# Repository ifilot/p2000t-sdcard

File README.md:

# P2000T SD-CARD cartridge

## Table of contents

* [Purpose](#purpose)
* [Downloads](#downloads)
* [How it functions](#how-it-functions)
* [Images](#images)
* [Commands](#commands)
* [Compilation instructions](#compilation-instructions)
* [Repository contents](#repository-contents)
* [Building the hardware](#building-the-hardware)
* [Ordering a cartridge](#ordering-a-cartridge)
* [Internal SD-card board](#internal-sd-card-board)
* [Formatting SD-card](#formatting-sd-card)
* [License](#license)

> [!TIP] 
> Have questions or comments about the **P2000T SD-card cartridge**? Join
> the conversation and chat with the developers on our [Discord
> server](https://discord.gg/YtzJTWYAxy).

## YouTube

Check out the YouTube video below for a detailed review of the SD-card cartridge.

## Purpose

Perhaps the most elegant solution for loading CAS files into your P2000T or
making backups of your tapes is via a cartridge that hosts an SD-card slot. Even
the smallest SD-cards have enough capacity to store the complete P2000T tape
archive. Reading from such an SD-card is non-trivial and requires both a
hardware solution to interface with the I/O port of the P2000T as well as a
software solution to navigate through the files hosted on a FAT32 partition.
This repository contains the PCB for interfacing a P2000T with an SD-card and
the necessary software routines to grab .CAS files from said SD card and load
them into memory.

> [!TIP]
> **Documentation**
> * Detailed documentation included how-to procedures can be found [here](https://www.philips-p2000t.nl/cartridges/sdcard-cartridge.html#sdcard-cartridge)
> * There is also a [manual in Dutch](https://github.com/ifilot/P2000T-SD-kaart-handleiding)  available.

## Downloads 

Read the section ["How it functions"](#how-it-functions) to understand what each
download file does.

> [!WARNING] 
> The files shown here cater specifically to PCB version 6 or later
> where the SD-card listens to I/O port 0x4X. Earlier version of the PCB are no
> longer actively maintained.

* [BASICBOOTSTRAP.BIN](https://github.com/ifilot/p2000t-sdcard/releases/download/latest-stable/BASICBOOTSTRAP.BIN)
* [FLASHER.BIN](https://github.com/ifilot/p2000t-sdcard/releases/download/latest-stable/FLASHER.BIN)
* [LAUNCHER.BIN](https://github.com/ifilot/p2000t-sdcard/releases/download/latest-stable/LAUNCHER.BIN)

> [!TIP]
> * Precompiled SD-card images, including flashing instructions, can be found [here](https://github.com/ifilot/p2000t-sdcard-image)
> * A list of PRG programs, specifically designed to operate with the SD-card cartridge, can be found [here](https://github.com/ifilot/p2000t-sdcard-cartridge-programs)

## How it functions

To interface with the SD-card, an SD-card slot is connected to the I/O port of
the P2000T. Interfacing with the SD-card proceeds via the SPI protocol which is
encoded in hardware (in contrast to bit-banging the protocol in software). From
the perspective of the P2000T, simple 1-byte instructions can be sent and
retrieved from the SD-card. By sending specific commands, data is sent or
retrieved from the SD-card.

While the SLOT2 cartridge (which hooks up to the I/O port of the P2000T) hosts
the circuitry to interface with the SD-card, a SLOT1 cartridge is required that
hosts the software. In order to run BASIC programs that are stored on the
SD-card as `.CAS` files, the regular BASIC environment **and** the required
routines to interface with the SD-card need to be present in memory. For this
reason, a modified version of the BASIC environment is used which upon boot will
load a launcher application from the ROM chip on the SLOT2 cartridge into main
memory. This launcher application allows the user to navigate the SD-card and
load BASIC programs into memory and run these. Detailed instructions on this
process are found [here](https://www.philips-p2000t.nl/cartridges/sdcard-cartridge.html#launching-cas-programs-from-the-sd-card-cartridge).

The launcher application needs to be placed on the ROM chip by means of a
flasher program. The flasher program is a different SLOT1 cartridge which can be
downloaded from the [download section](#downloads). The flasher program will
copy a `LAUNCHER.BIN` file from the root folder of the SD-card to the ROM chip
on the SLOT2 cartridge. This procedure is also used to update the launcher
application. Details on this process can be found [here](https://www.philips-p2000t.nl/cartridges/sdcard-cartridge.html#flashing-the-launcher-onto-the-rom-chip).

It is also possible to make copies of existing tapes to the SD-card. For this
purpose, a `CASDUMP.PRG` program is written. These special types of programs can
be loaded from the SD-card and executes via the launcher application. After
completion, one automatically returns to the launcher, allowing one to load one
of the freshly copied programs.

## Images

SLOT2 cartridge enclosure and populated PCB.

Screenshots of navigation and execution of .CAS files.

## Commands

Upon booting into the LAUNCHER application, the user interfaces with the SD-card
using a set of short commands. Below, the list of commands is provided

| **Command**         | **Description**                                                   |
| ------------------- | ------------------------------------------------------------------|
| `ls`                | List contents of current folder                                   |
| `lscas`             | List contents of current folder, listing contents of CAS files    |
| `cd <number>`       | Change directory                                                  |
| `run <number>`      | Run .CAS file                                                     |
| `hexdump <number>`  | Performs a 120-byte hexdump of a file                             |
| `fileinfo <number>` | Provides location details of a file                               |
| `ledtest`           | Performs a quick test on the read/write LEDs                      |
| `stack`             | Show current position of the stack pointer                        |
| `dump<XXXX>`        | Perform a 120-byte hexdump of main memory starting at `0xXXXX`    |
| `romdump<XXXX>`     | Perform a 120-byte hexdump of cartridge ROM starting at `0xXXXX`  |
| `ramdump<XXXX>`     | Perform a 120-byte hexdump of cartridge RAM starting at `0xXXXX`  |

Note that `<number>` needs to replaced with the specific number of a file. Users
who are familiar with command line interfaces are probably used to specifying
filenames rather than numbers. This reason this approach was chosen is mainly
because it is simpler to program and furthermore a bit quicker to type.

## Compilation instructions

Compilation is done using the [z88dk Docker](https://hub.docker.com/r/z88dk/z88dk)
by means of `compile.sh`. To compile the launcher, run

```bash
cd src
./compile launcher
```

and for the flasher utility

```bash
cd src
./compile flasher
```

## Repository contents

* [Cartridge cases](cases/)
* [PCB layout files (KiCAD)](pcb/port2-sdcard-interface/)
* [Modified BASIC ROM source files](basicmod/)
* [Launcher and Flasher programs](src/)
* [Custom programs](programs/)

## Building the hardware

### Gerber files

To create your own SLOT2 cartridge, download the GERBER files from
[here](pcb/port2-sdcard-interface/GERBERS/), put them in a `.ZIP` file and send
them to your favorite PCB print farm. The author of this repository mainly uses
[JLCPCB](https://jlcpcb.com/), but plenty of alternatives are available. The
SLOT2 PCB has four layers. It is recommended to apply an ENIG (gold) coating and
chamfer the edge connector for facile insertion into the P2000T. After ordering,
one needs to either hand-solder the components (which can be tricky for the SMD
chips) or alternatively make use of an assembly service by which the PCB print
farm will solder these components for you.

### PCB assembly service

The folder [pcb/port2-sdcard-interface](pcb/port2-sdcard-interface) contains
`port2-sdcard-interface_bom_bot.csv` and `port2-sdcard-interface-bottom-pos.csv`
which can be used for the JLCPCB assembly service. An example of the part
placement can be found in the image below. At the time of writing, two
components were unavailable, being the memory chip `62128` and a 0 ohm resistor,
which is the reason that these two parts are missing. Note that all through-hole
parts, e.g. LEDs, oscillator and PLCC32 socket, have to be hand-soldered in.

### Ordering a cartridge

It is also possible to order a cartridge (typically there are always a few
of them in stock). If you are interested, feel free to contact the author of
this repository at `ivo at ivofilot dot nl` to discuss pricing and shipping.

## Internal SD-card board

This project also includes an [internal SD-card
board](pcb/internal-sdcard-interface/) designed to mount on top of the main
baseboard inside the P2000T. In addition to the SD-card reader functionality,
the board also provides 64 KiB of additional memory, making it an all-in-one
solution.

To install this board, you will need two custom brackets. You can find the
necessary bracket files [here](brackets).

## Formatting SD-card

The way that the SD-card is formatted is critical. The SD-card needs be
formatted using a MBR/FAT32 partition. Often, directly formatting the SD-card
via Windows Explorer or similar works well, but sometimes a more rigorous
procedure is needed, which is explained below.

1. Type `WINDOWS + R` and run `CMD`.
2. Run `diskpart`.
3. Type `list disk` followed by `select disk <NR>` where `<NR>` corresponds to
   your SD-card.
4. Type `clean`. You get a response with `DiskPart succeeded in cleaning the
   disk.`.
5. Type `list volume`, followed by `select volume <ID>` where `<ID>` corresponds
   to your SD-card drive.
6. Type `convert mbr`. You should get the response `DiskPart successfully
   converted the selected disk to MBR format.`.
7. Type `create partition primary`. The response should be `DiskPart succeeded
   in creating the specified partition.`.
8. Finally, type `format fs=fat32 quick label="P2000T"`, after which the
   response is `DiskPart successfully formatted the volume.`.

Your SD-card should now be ready to work in the SD-cartridge. Of course, you
still need to copy files to it in order to load something of it.

## License

* All software is shared under the [GPL v3 license](https://www.gnu.org/licenses/gpl-3.0).
* All hardware (e.g. KiCAD files and .stl files) are shared under the [CERN-OHL-S license](https://ohwr.org/project/cernohl/-/wikis/uploads/819d71bea3458f71fba6cf4fb0f2de6b/cern_ohl_s_v2.txt).
* All documentation is shared under the [CC-BY-SA 4.0 license](https://creativecommons.org/licenses/by-sa/4.0/).

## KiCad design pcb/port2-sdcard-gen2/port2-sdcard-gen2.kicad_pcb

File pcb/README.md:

# PCB

This folder contains the PCBs for the [SLOT2 SD-card cartridge](port2-sdcard-interface) 
and also for a [SD-card interface prototype PCB](sdcard-prototype). 
The latter is only used for development purposes and can be ignored if one is 
solely interested in building a SLOT2 cartridge.

## Bill of materials

* 1 x CY62128ELL-45SXI
* 3 x 74HC00
* 2 x 74HC74
* 1 x 74HC163
* 2 x 74HC138
* 1 x 74HC123
* 2 x 74HC273
* 2 x 74HC32
* 1 x HC165
* 1 x HC595
* 1 x SST39SF010
* 1 x 74HC02
* 1 x 74HC85
* 1 x 16MHz crystal oscillator

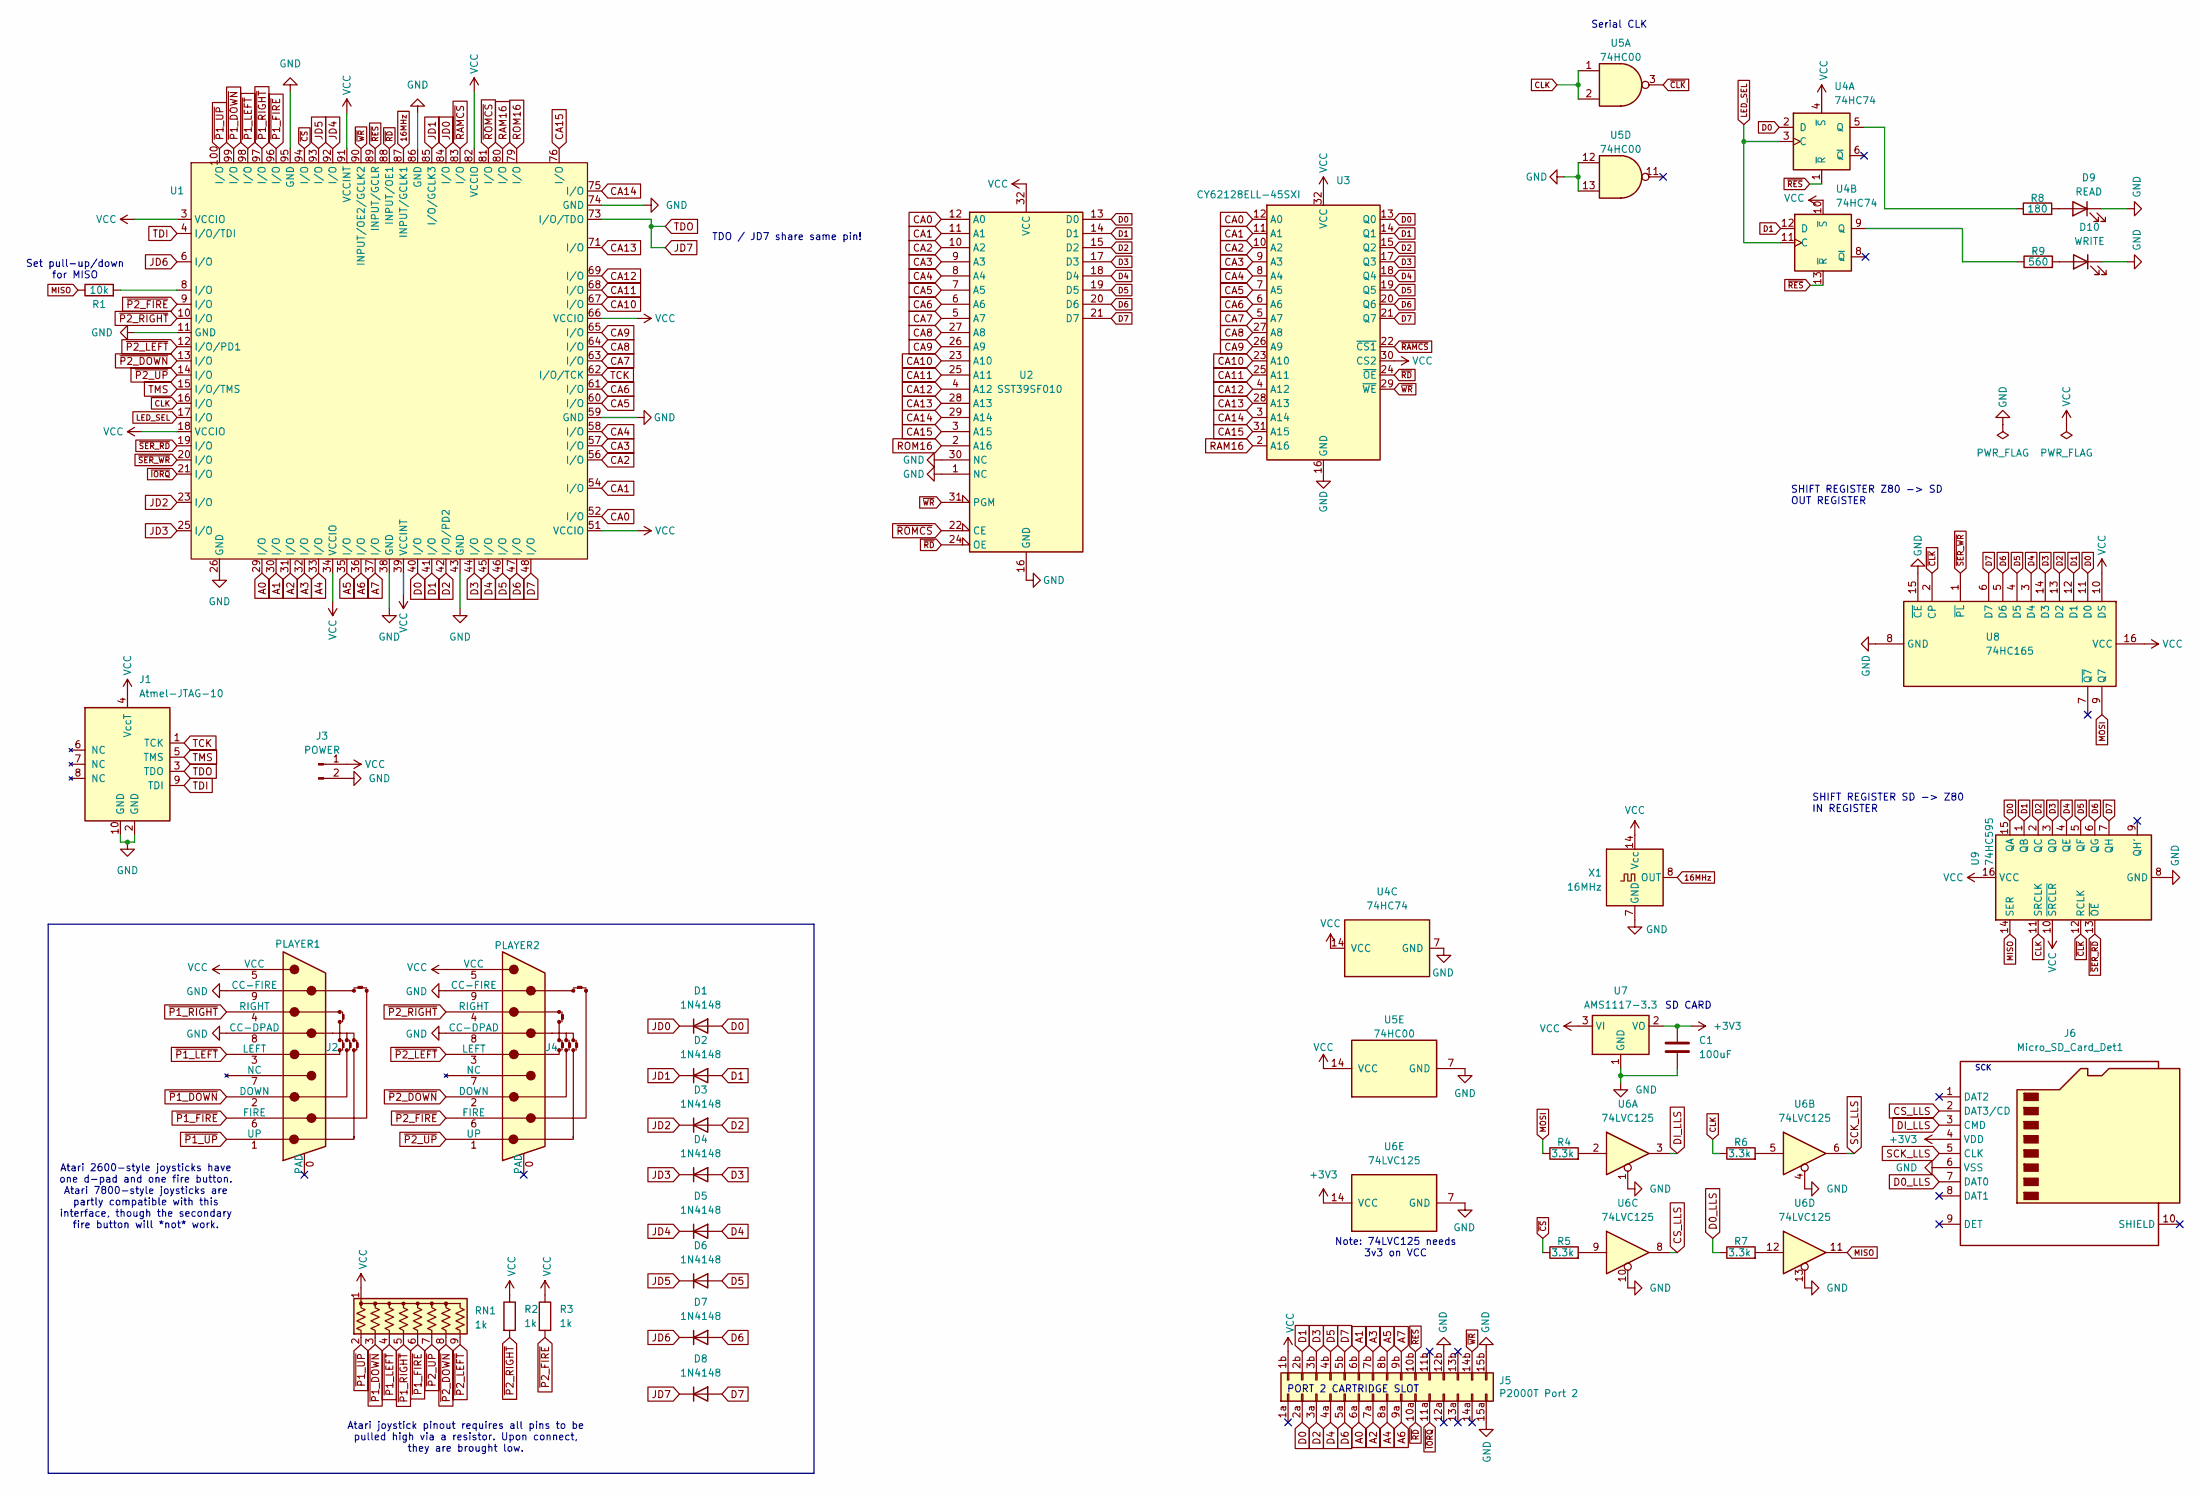
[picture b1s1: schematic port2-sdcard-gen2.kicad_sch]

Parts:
C1: 100uF; C_1206_3216Metric_Pad1.33x1.80mm_HandSolder; LCSC Part # C309030
D1, D2, D3, D4, D5, D6, D7, D8: 1N4148; D_DO-35_SOD27_P7.62mm_Horizontal
D9: READ; LED_0805_2012Metric_Pad1.15x1.40mm_HandSolder
D10: WRITE; LED_0805_2012Metric_Pad1.15x1.40mm_HandSolder
J1: Atmel-JTAG-10; IDC-Header_2x05_P2.54mm_Vertical
J2: PLAYER1; DSUB-9_Pins_Horizontal_P2.77x2.84mm_EdgePinOffset4.94mm_Hou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
J3: POWER
J4: PLAYER2; DSUB-9_Pins_Horizontal_P2.77x2.84mm_EdgePinOffset4.94mm_Hou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
J5: P2000T Port 2; p2000t_cartridge_edge
J6: Micro_SD_Card_Det1; CONN9_MSD-1_CUD; LCSC Part # C381082
R1: 10k; R_0805_2012Metric_Pad1.20x1.40mm_HandSolder
R2, R3: 1k; R_Axial_DIN0207_L6.3mm_D2.5mm_P7.62mm_Horizontal
R4, R5, R6, R7: 3.3k; R_0805_2012Metric_Pad1.20x1.40mm_HandSolder; LCSC Part # C407459
R8: 180; R_0805_2012Metric_Pad1.20x1.40mm_HandSolder; LCSC Part # C429158
R9: 560; R_0805_2012Metric_Pad1.20x1.40mm_HandSolder; LCSC Part # C429158
RN1: 1k; R_Array_SIP9
U1: TQFP-100_14x14mm_P0.5mm
U2: SST39SF010; PLCC-32_THT-Socket
U3: CY62128ELL-45SXI; SOP-32_11.305x20.495mm_P1.27mm; LCSC Part # C2840304
U4: 74HC74; SO-14_3.9x8.65mm_P1.27mm; LCSC Part # C27597
U5: 74HC00; SO-14_3.9x8.65mm_P1.27mm; LCSC Part # C699445
U6: 74LVC125; TSSOP-14_4.4x5mm_P0.65mm; LCSC Part # C7494906
U7: AMS1117-3.3; SOT-223-3_TabPin2; LCSC Part # C5346136
U8: 74HC165; SOIC-16_3.9x9.9mm_P1.27mm; LCSC Part # C5613
U9: 74HC595; SOIC-16_3.9x9.9mm_P1.27mm; LCSC Part # C5947
X1: 16MHz; Oscillator_DIP-14

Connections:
16MHz: U1.87 (INPUT/GCLK1), X1.8 (OUT)
+3V3: C1.1, J6.4 (VDD), U6.14 (VCC), U7.2 (VO)
A0: J5.6a, U1.29 (I/O)
A1: J5.6b, U1.30 (I/O)
A2: J5.7a, U1.31 (I/O)
A3: J5.7b, U1.32 (I/O)
A4: J5.8a, U1.33 (I/O)
A5: J5.8b, U1.35 (I/O)
A6: J5.9a, U1.36 (I/O)
A7: J5.9b, U1.37 (I/O)
CA0: U1.52 (I/O), U2.12 (A0), U3.12 (A0)
CA1: U1.54 (I/O), U2.11 (A1), U3.11 (A1)
CA2: U1.56 (I/O), U2.10 (A2), U3.10 (A2)
CA3: U1.57 (I/O), U2.9 (A3), U3.9 (A3)
CA4: U1.58 (I/O), U2.8 (A4), U3.8 (A4)
CA5: U1.60 (I/O), U2.7 (A5), U3.7 (A5)
CA6: U1.61 (I/O), U2.6 (A6), U3.6 (A6)
CA7: U1.63 (I/O), U2.5 (A7), U3.5 (A7)
CA8: U1.64 (I/O), U2.27 (A8), U3.27 (A8)
CA9: U1.65 (I/O), U2.26 (A9), U3.26 (A9)
CA10: U1.67 (I/O), U2.23 (A10), U3.23 (A10)
CA11: U1.68 (I/O), U2.25 (A11), U3.25 (A11)
CA12: U1.69 (I/O), U2.4 (A12), U3.4 (A12)
CA13: U1.71 (I/O), U2.28 (A13), U3.28 (A13)
CA14: U1.75 (I/O), U2.29 (A14), U3.3 (A14)
CA15: U1.76 (I/O), U2.3 (A15), U3.31 (A15)
CLK: R6.1, U1.16 (I/O), U5.1, U5.2, U9.11 (SRCLK)
CS_LLS: J6.2 (DAT3/CD), U6.8
D0: D1.2 (A), J5.2a, U1.40 (I/O), U2.13 (D0), U3.13 (Q0), U4.2 (D), U8.11 (D0), U9.15 (QA)
D0_LLS: J6.7 (DAT0), R7.1
D1: D2.2 (A), J5.2b, U1.41 (I/O), U2.14 (D1), U3.14 (Q1), U4.12 (D), U8.12 (D1), U9.1 (QB)
D2: D3.2 (A), J5.3a, U1.42 (I/O/PD2), U2.15 (D2), U3.15 (Q2), U8.13 (D2), U9.2 (QC)
D3: D4.2 (A), J5.3b, U1.44 (I/O), U2.17 (D3), U3.17 (Q3), U8.14 (D3), U9.3 (QD)
D4: D5.2 (A), J5.4a, U1.45 (I/O), U2.18 (D4), U3.18 (Q4), U8.3 (D4), U9.4 (QE)
D5: D6.2 (A), J5.4b, U1.46 (I/O), U2.19 (D5), U3.19 (Q5), U8.4 (D5), U9.5 (QF)
D6: D7.2 (A), J5.5a, U1.47 (I/O), U2.20 (D6), U3.20 (Q6), U8.5 (D6), U9.6 (QG)
D7: D8.2 (A), J5.5b, U1.48 (I/O), U2.21 (D7), U3.21 (Q7), U8.6 (D7), U9.7 (QH)
DI_LLS: J6.3 (CMD), U6.3
GND: C1.2, D9.1 (K), D10.1 (K), J1.2 (GND), J1.10 (GND), J2.8 (CC-DPAD), J2.9 (CC-FIRE), J3.2, J4.8 (CC-DPAD), J4.9 (CC-FIRE), J5.12b, J5.15a, J5.15b, J6.6 (VSS), U1.11 (GND), U1.26 (GND), U1.38 (GND), U1.43 (GND), U1.59 (GND), U1.74 (GND), U1.86 (GND), U1.95 (GND), U2.1 (NC), U2.16 (GND), U2.30 (NC), U3.16 (GND), U4.7 (GND), U5.7 (GND), U5.12, U5.13, U6.1, U6.4, U6.7 (GND), U6.10, U6.13, U7.1 (GND), U8.8 (GND), U8.15 (~CE), U9.8 (GND), X1.7 (GND)
JD0: D1.1 (K), U1.84 (I/O)
JD1: D2.1 (K), U1.85 (I/O/GCLK3)
JD2: D3.1 (K), U1.23 (I/O)
JD3: D4.1 (K), U1.25 (I/O)
JD4: D5.1 (K), U1.92 (I/O)
JD5: D6.1 (K), U1.93 (I/O)
JD6: D7.1 (K), U1.6 (I/O)
JD7: D8.1 (K), J1.3 (TDO), U1.73 (I/O/TDO)
LED_SEL: U1.17 (I/O), U4.3 (C), U4.11 (C)
MISO: R1.1, U6.11, U9.14 (SER)
MOSI: R4.1, U8.9 (Q7)
unnamed: D9.2 (A), R8.2
unnamed: D10.2 (A), R9.2
unnamed: R1.2, U1.8 (I/O)
unnamed: R4.2, U6.2
unnamed: R5.2, U6.9
unnamed: R6.2, U6.5
unnamed: R7.2, U6.12
unnamed: R8.1, U4.5 (Q)
unnamed: R9.1, U4.9 (Q)
RAM16: U1.80 (I/O), U3.2 (A16)
ROM16: U1.79 (I/O), U2.2 (A16)
SCK_LLS: J6.5 (CLK), U6.6
TCK: J1.1 (TCK), U1.62 (I/O/TCK)
TDI: J1.9 (TDI), U1.4 (I/O/TDI)
TMS: J1.5 (TMS), U1.15 (I/O/TMS)
VCC: J1.4 (VccT), J2.5 (VCC), J3.1, J4.5 (VCC), J5.1b, R2.1, R3.1, RN1.1 (common), U1.3 (VCCIO), U1.18 (VCCIO), U1.34 (VCCIO), U1.39 (VCCINT), U1.51 (VCCIO), U1.66 (VCCIO), U1.82 (VCCIO), U1.91 (VCCINT), U2.32 (VCC), U3.30 (CS2), U3.32 (VCC), U4.4 (~S), U4.10 (~S), U4.14 (VCC), U5.14 (VCC), U7.3 (VI), U8.10 (DS), U8.16 (VCC), U9.10 (~SRCLR), U9.16 (VCC), X1.14 (Vcc)
~CLK: U5.3, U8.2 (CP), U9.12 (RCLK)
~CS: R5.1, U1.94 (I/O)
~IORQ: J5.11a, U1.21 (I/O)
~P1_DOWN: J2.2 (DOWN), RN1.3 (R2), U1.99 (I/O)
~P1_FIRE: J2.6 (FIRE), RN1.6 (R5), U1.96 (I/O)
~P1_LEFT: J2.3 (LEFT), RN1.4 (R3), U1.98 (I/O)
~P1_RIGHT: J2.4 (RIGHT), RN1.5 (R4), U1.97 (I/O)
~P1_UP: J2.1 (UP), RN1.2 (R1), U1.100 (I/O)
~P2_DOWN: J4.2 (DOWN), RN1.8 (R7), U1.13 (I/O)
~P2_FIRE: J4.6 (FIRE), R3.2, U1.9 (I/O)
~P2_LEFT: J4.3 (LEFT), RN1.9 (R8), U1.12 (I/O/PD1)
~P2_RIGHT: J4.4 (RIGHT), R2.2, U1.10 (I/O)
~P2_UP: J4.1 (UP), RN1.7 (R6), U1.14 (I/O)
~RAMCS: U1.83 (I/O), U3.22 (~CS1)
~RD: J5.10a, U1.88 (INPUT/OE1), U2.24 (OE), U3.24 (~OE)
~RES: J5.10b, U1.89 (INPUT/GCLR), U4.1 (~R), U4.13 (~R)
~ROMCS: U1.81 (I/O), U2.22 (CE)
~SER_RD: U1.19 (I/O), U9.13 (~OE)
~SER_WR: U1.20 (I/O), U8.1 (~PL)
~WR: J5.14b, U1.90 (INPUT/OE2/GCLK2), U2.31 (PGM), U3.29 (~WE)

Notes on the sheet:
SHIFT REGISTER Z80 -> SD OUT REGISTER
Serial CLK
PORT 2 CARTRIDGE SLOT
SCK
SHIFT REGISTER SD -> Z80 IN REGISTER
Atari 2600-style joysticks have one d-pad and one fire button. Atari 7800-style joysticks are partly compatible with this interface, though the secondary fire button will *not* work.
SD CARD
TDO / JD7 share same pin!
Atari joystick pinout requires all pins to be pulled high via a resistor. Upon connect, they are brought low.
Set pull-up/down for MISO
Note: 74LVC125 needs 3v3 on VCC

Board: 2 copper layers, 36 parts (31 on the bottom side), 86 nets, no tracks yet.

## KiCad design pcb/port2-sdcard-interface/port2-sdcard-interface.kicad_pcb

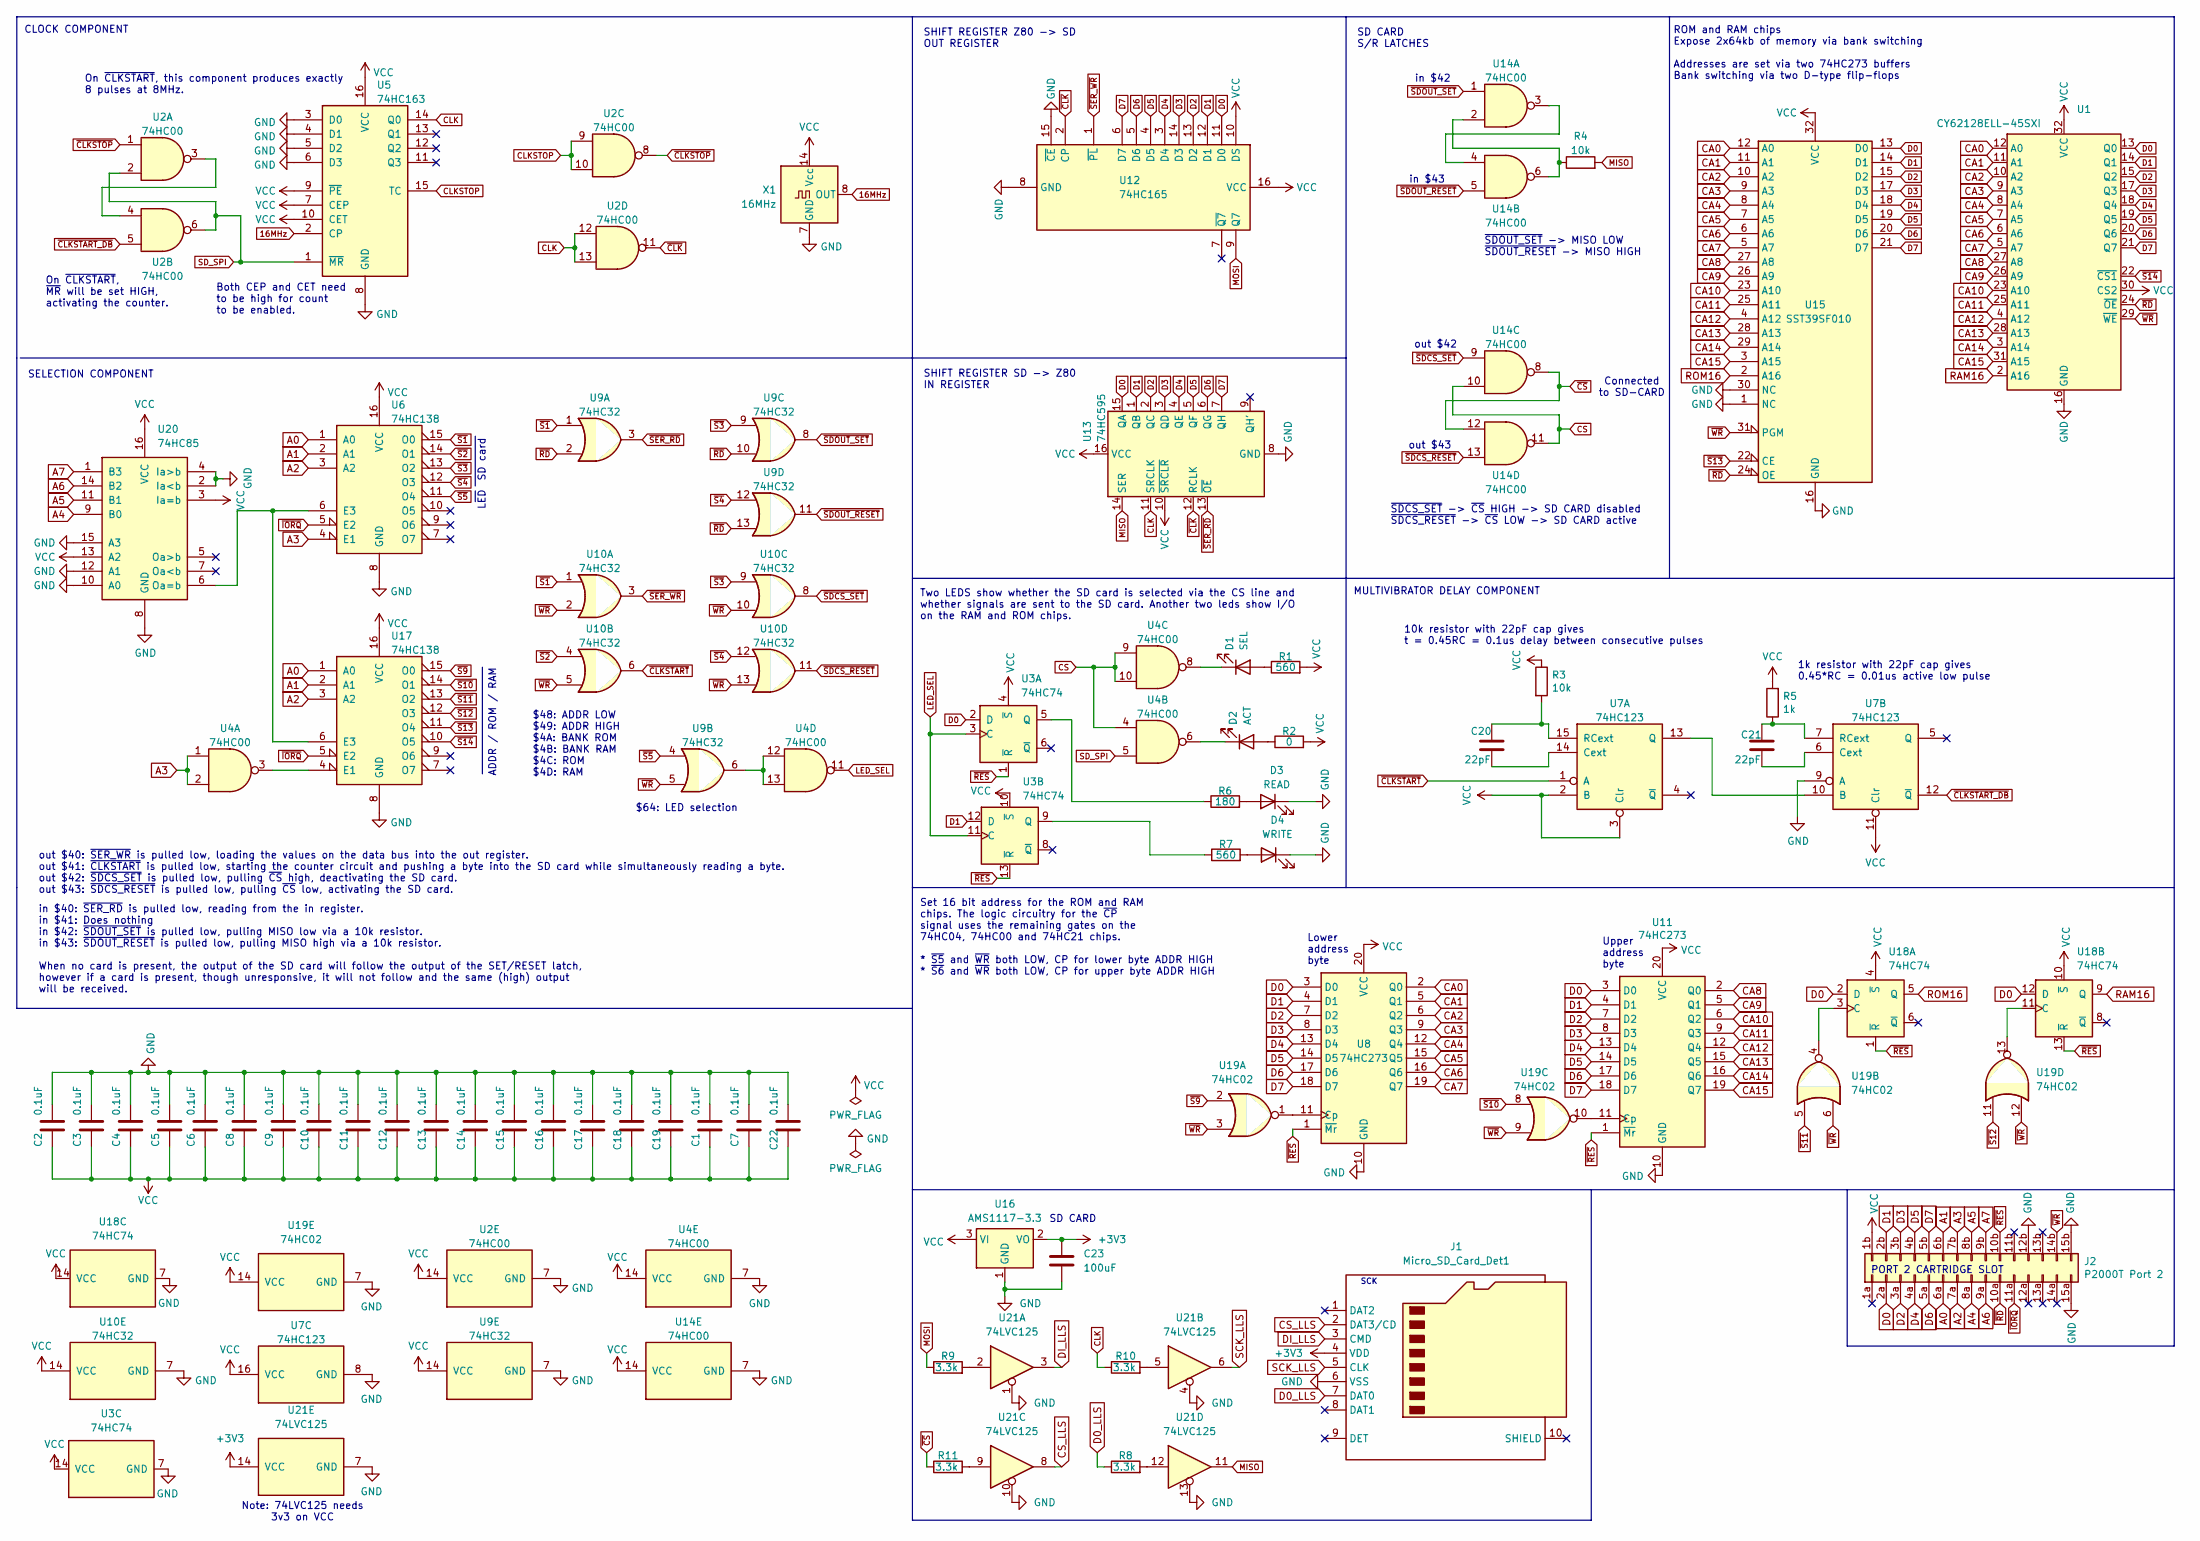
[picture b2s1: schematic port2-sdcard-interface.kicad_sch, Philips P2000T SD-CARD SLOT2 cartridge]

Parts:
C1, C2, C3, C4, C5, C6, C7, C8, C9, C10, C11, C12, C13, C14, C15, C16, C17, C18, C19, C22: 0.1uF; C_0805_2012Metric_Pad1.18x1.45mm_HandSolder; LCSC Part # C126469
C20, C21: 22pF; C_0805_2012Metric_Pad1.18x1.45mm_HandSolder; LCSC Part # C525286
C23: 100uF; C_1206_3216Metric_Pad1.33x1.80mm_HandSolder; LCSC Part # C309030
D1: SEL; LED_D5.0mm
D2: ACT; LED_D5.0mm
D3: READ; LED_D5.0mm
D4: WRITE; LED_D5.0mm
J1: Micro_SD_Card_Det1; CONN9_MSD-1_CUD; LCSC Part # C381082
J2: P2000T Port 2; p2000t_cartridge_edge
R1, R7: 560; R_0805_2012Metric_Pad1.20x1.40mm_HandSolder; LCSC Part # C429158
R2: 0; R_0805_2012Metric_Pad1.20x1.40mm_HandSolder; LCSC Part # C431818
R3, R4: 10k; R_0805_2012Metric_Pad1.20x1.40mm_HandSolder; LCSC Part # C5159708
R5: 1k; R_0805_2012Metric_Pad1.20x1.40mm_HandSolder; LCSC Part # C5123594
R6: 180; R_0805_2012Metric_Pad1.20x1.40mm_HandSolder; LCSC Part # C429158
R8, R9, R10, R11: 3.3k; R_0805_2012Metric_Pad1.20x1.40mm_HandSolder; LCSC Part # C407459
U1: CY62128ELL-45SXI; SSOP-32_11.305x20.495mm_P1.27mm; LCSC Part # C2840304
U2, U4, U14: 74HC00; SO-14_3.9x8.65mm_P1.27mm; LCSC Part # C699445
U3, U18: 74HC74; SO-14_3.9x8.65mm_P1.27mm; LCSC Part # C27597
U5: 74HC163; SOIC-16_3.9x9.9mm_P1.27mm; LCSC Part # C338758
U6, U17: 74HC138; SOIC-16_3.9x9.9mm_P1.27mm; LCSC Part # C5602
U7: 74HC123; SOIC-16_3.9x9.9mm_P1.27mm; LCSC Part # C5597
U8, U11: 74HC273; SOIC-20W_7.5x12.8mm_P1.27mm; LCSC Part # C131486
U9, U10: 74HC32; SO-14_3.9x8.65mm_P1.27mm; LCSC Part # C5632
U12: 74HC165; SOIC-16_3.9x9.9mm_P1.27mm; LCSC Part # C5613
U13: 74HC595; SOIC-16_3.9x9.9mm_P1.27mm; LCSC Part # C5947
U15: SST39SF010; PLCC-32_THT-Socket
U16: AMS1117-3.3; SOT-223-3_TabPin2; LCSC Part # C5346136
U19: 74HC02; SO-14_3.9x8.65mm_P1.27mm; LCSC Part # C5588
U20: 74HC85; SOIC-16_3.9x9.9mm_P1.27mm; LCSC Part # C5953
U21: 74LVC125; TSSOP-14_4.4x5mm_P0.65mm; LCSC Part # C7494906
X1: 16MHz; Oscillator_DIP-14

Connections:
16MHz: U5.2 (CP), X1.8 (OUT)
+3V3: C23.1, J1.4 (VDD), U16.2 (VO), U21.14 (VCC)
A0: J2.6a, U6.1 (A0), U17.1 (A0)
A1: J2.6b, U6.2 (A1), U17.2 (A1)
A2: J2.7a, U6.3 (A2), U17.3 (A2)
A3: J2.7b, U4.1, U4.2, U6.4 (E1)
A4: J2.8a, U20.9 (B0)
A5: J2.8b, U20.11 (B1)
A6: J2.9a, U20.14 (B2)
A7: J2.9b, U20.1 (B3)
CA0: U1.12 (A0), U8.2 (Q0), U15.12 (A0)
CA1: U1.11 (A1), U8.5 (Q1), U15.11 (A1)
CA2: U1.10 (A2), U8.6 (Q2), U15.10 (A2)
CA3: U1.9 (A3), U8.9 (Q3), U15.9 (A3)
CA4: U1.8 (A4), U8.12 (Q4), U15.8 (A4)
CA5: U1.7 (A5), U8.15 (Q5), U15.7 (A5)
CA6: U1.6 (A6), U8.16 (Q6), U15.6 (A6)
CA7: U1.5 (A7), U8.19 (Q7), U15.5 (A7)
CA8: U1.27 (A8), U11.2 (Q0), U15.27 (A8)
CA9: U1.26 (A9), U11.5 (Q1), U15.26 (A9)
CA10: U1.23 (A10), U11.6 (Q2), U15.23 (A10)
CA11: U1.25 (A11), U11.9 (Q3), U15.25 (A11)
CA12: U1.4 (A12), U11.12 (Q4), U15.4 (A12)
CA13: U1.28 (A13), U11.15 (Q5), U15.28 (A13)
CA14: U1.3 (A14), U11.16 (Q6), U15.29 (A14)
CA15: U1.31 (A15), U11.19 (Q7), U15.3 (A15)
CLK: R10.1, U2.12, U2.13, U5.14 (Q0), U13.11 (SRCLK)
CLKSTOP: U2.9, U2.10, U5.15 (TC)
CS: U4.4, U4.9, U4.10, U14.10, U14.11
CS_LLS: J1.2 (DAT3/CD), U21.8
D0: J2.2a, U1.13 (Q0), U3.2 (D), U8.3 (D0), U11.3 (D0), U12.11 (D0), U13.15 (QA), U15.13 (D0), U18.2 (D), U18.12 (D)
D0_LLS: J1.7 (DAT0), R8.1
D1: J2.2b, U1.14 (Q1), U3.12 (D), U8.4 (D1), U11.4 (D1), U12.12 (D1), U13.1 (QB), U15.14 (D1)
D2: J2.3a, U1.15 (Q2), U8.7 (D2), U11.7 (D2), U12.13 (D2), U13.2 (QC), U15.15 (D2)
D3: J2.3b, U1.17 (Q3), U8.8 (D3), U11.8 (D3), U12.14 (D3), U13.3 (QD), U15.17 (D3)
D4: J2.4a, U1.18 (Q4), U8.13 (D4), U11.13 (D4), U12.3 (D4), U13.4 (QE), U15.18 (D4)
D5: J2.4b, U1.19 (Q5), U8.14 (D5), U11.14 (D5), U12.4 (D5), U13.5 (QF), U15.19 (D5)
D6: J2.5a, U1.20 (Q6), U8.17 (D6), U11.17 (D6), U12.5 (D6), U13.6 (QG), U15.20 (D6)
D7: J2.5b, U1.21 (Q7), U8.18 (D7), U11.18 (D7), U12.6 (D7), U13.7 (QH), U15.21 (D7)
DI_LLS: J1.3 (CMD), U21.3
GND: C1.2, C2.2, C3.2, C4.2, C5.2, C6.2, C7.2, C8.2, C9.2, C10.2, C11.2, C12.2, C13.2, C14.2, C15.2, C16.2, C17.2, C18.2, C19.2, C22.2, C23.2, D3.1 (K), D4.1 (K), J1.6 (VSS), J2.12b, J2.15a, J2.15b, U1.16 (GND), U2.7 (GND), U3.7 (GND), U4.7 (GND), U5.3 (D0), U5.4 (D1), U5.5 (D2), U5.6 (D3), U5.8 (GND), U6.8 (GND), U7.8 (GND), U7.9 (A), U8.10 (GND), U9.7 (GND), U10.7 (GND), U11.10 (GND), U12.8 (GND), U12.15 (~CE), U13.8 (GND), U14.7 (GND), U15.1 (NC), U15.16 (GND), U15.30 (NC), U16.1 (GND), U17.8 (GND), U18.7 (GND), U19.7 (GND), U20.2 (Ia<b), U20.4 (Ia>b), U20.8 (GND), U20.10 (A0), U20.12 (A1), U20.15 (A3), U21.1, U21.4, U21.7 (GND), U21.10, U21.13, X1.7 (GND)
LED_SEL: U3.3 (C), U3.11 (C), U4.11
MISO: R4.2, U13.14 (SER), U21.11
MOSI: R9.1, U12.9 (Q7)
unnamed: D1.2 (A), R1.1
unnamed: D1.1 (K), U4.8
unnamed: D2.2 (A), R2.1
unnamed: D2.1 (K), U4.6
unnamed: D3.2 (A), R6.2
unnamed: D4.2 (A), R7.2
unnamed: R4.1, U14.2, U14.6
unnamed: R8.2, U21.12
unnamed: R9.2, U21.2
unnamed: R10.2, U21.5
unnamed: R11.2, U21.9
unnamed: U2.3, U2.4
unnamed: R6.1, U3.5 (Q)
unnamed: R7.1, U3.9 (Q)
unnamed: U4.12, U4.13, U9.6
unnamed: C20.1, U7.14 (Cext)
unnamed: U7.10 (B), U7.13 (Q)
unnamed: C20.2, R3.2, U7.15 (RCext)
unnamed: C21.1, U7.6 (Cext)
unnamed: C21.2, R5.1, U7.7 (RCext)
unnamed: U8.11 (Cp), U19.1
unnamed: U11.11 (Cp), U19.10
unnamed: U14.3, U14.4
unnamed: U4.3, U17.4 (E1)
unnamed: U6.6 (E3), U17.6 (E3), U20.6 (Oa=b)
unnamed: U18.3 (C), U19.4
unnamed: U18.11 (C), U19.13
RAM16: U1.2 (A16), U18.9 (Q)
ROM16: U15.2 (A16), U18.5 (Q)
SCK_LLS: J1.5 (CLK), U21.6
SD_SPI: U2.2, U2.6, U4.5, U5.1 (~MR)
VCC: C1.1, C2.1, C3.1, C4.1, C5.1, C6.1, C7.1, C8.1, C9.1, C10.1, C11.1, C12.1, C13.1, C14.1, C15.1, C16.1, C17.1, C18.1, C19.1, C22.1, J2.1b, R1.2, R2.2, R3.1, R5.2, U1.30 (CS2), U1.32 (VCC), U2.14 (VCC), U3.4 (~S), U3.10 (~S), U3.14 (VCC), U4.14 (VCC), U5.7 (CEP), U5.9 (~PE), U5.10 (CET), U5.16 (VCC), U6.16 (VCC), U7.2 (B), U7.3 (Clr), U7.11 (Clr), U7.16 (VCC), U8.20 (VCC), U9.14 (VCC), U10.14 (VCC), U11.20 (VCC), U12.10 (DS), U12.16 (VCC), U13.10 (~SRCLR), U13.16 (VCC), U14.14 (VCC), U15.32 (VCC), U16.3 (VI), U17.16 (VCC), U18.4 (~S), U18.10 (~S), U18.14 (VCC), U19.14 (VCC), U20.3 (Ia=b), U20.13 (A2), U20.16 (VCC), X1.14 (Vcc)
~CLKSTART_DB: U2.5, U7.12 (~Q)
~CLKSTART: U7.1 (A), U10.6
~CLKSTOP: U2.1, U2.8
~CLK: U2.11, U12.2 (CP), U13.12 (RCLK)
~CS: R11.1, U14.8, U14.12
~IORQ: J2.11a, U6.5 (E2), U17.5 (E2)
~RD: J2.10a, U1.24 (~OE), U9.2, U9.10, U9.13, U15.24 (OE)
~RES: J2.10b, U3.1 (~R), U3.13 (~R), U8.1 (~Mr), U11.1 (~Mr), U18.1 (~R), U18.13 (~R)
~S1: U6.15 (O0), U9.1, U10.1
~S2: U6.14 (O1), U10.4
~S3: U6.13 (O2), U9.9, U10.9
~S4: U6.12 (O3), U9.12, U10.12
~S5: U6.11 (O4), U9.4
~S9: U17.15 (O0), U19.2
~S10: U17.14 (O1), U19.8
~S11: U17.13 (O2), U19.5
~S12: U17.12 (O3), U19.11
~S13: U15.22 (CE), U17.11 (O4)
~S14: U1.22 (~CS1), U17.10 (O5)
~SDCS_RESET: U10.11, U14.13
~SDCS_SET: U10.8, U14.9
~SDOUT_RESET: U9.11, U14.5
~SDOUT_SET: U9.8, U14.1
~SER_RD: U9.3, U13.13 (~OE)
~SER_WR: U10.3, U12.1 (~PL)
~WR: J2.14b, U1.29 (~WE), U9.5, U10.2, U10.5, U10.10, U10.13, U15.31 (PGM), U19.3, U19.6, U19.9, U19.12

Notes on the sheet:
Note: 74LVC125 needs 3v3 on VCC
SD card
$64: LED selection
SHIFT REGISTER SD -> Z80 IN REGISTER
SD CARD S/R LATCHES
out $40: ~{SER_WR} is pulled low, loading the values on the data bus into the out register. out $41: ~{CLKSTART} is pulled low, starting the counter circuit and pushing a byte into the SD card while simultaneously reading a byte. out $42: ~{SDCS_SET} is pulled low, pulling ~{CS} high, deactivating 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
LED
On ~{CLKSTART}, this component produces exactly 8 pulses at 8MHz.
Set 16 bit address for the ROM and RAM chips. The logic circuitry for the ~{CP} signal uses the remaining gates on the 74HC04, 74HC00 and 74HC21 chips. * ~{S5} and ~{WR} both LOW, CP for lower byte ADDR HIGH * ~{S6} and ~{WR} both LOW, CP for upper byte ADDR HIGH
On ~{CLKSTART}, ~{MR} will be set HIGH, activating the counter.
Lower address byte
in $42
in $40: ~{SER_RD} is pulled low, reading from the in register. in $41: Does nothing in $42: ~{SDOUT_SET} is pulled low, pulling MISO low via a 10k resistor. in $43: ~{SDOUT_RESET} is pulled low, pulling MISO high via a 10k resistor. When no card is present, the output of the SD card will follow the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
Connected to SD-CARD
SD CARD
~{SDOUT_SET} -> MISO LOW ~{SDOUT_RESET} -> MISO HIGH
~{SDCS_SET} -> ~{CS} HIGH -> SD CARD disabled ~{SDCS_RESET} -> ~{CS} LOW -> SD CARD active
SELECTION COMPONENT
1k resistor with 22pF cap gives 0.45*RC = 0.01us active low pulse
10k resistor with 22pF cap gives t = 0.45RC = 0.1us delay between consecutive pulses
CLOCK COMPONENT
ADDR / ROM / RAM
in $43
Both CEP and CET need to be high for count to be enabled.
SCK
$48: ADDR LOW $49: ADDR HIGH $4A: BANK ROM $4B: BANK RAM $4C: ROM $4D: RAM
MULTIVIBRATOR DELAY COMPONENT
Upper address byte
PORT 2 CARTRIDGE SLOT
SHIFT REGISTER Z80 -> SD OUT REGISTER
out $42
out $43
Two LEDS show whether the SD card is selected via the CS line and whether signals are sent to the SD card. Another two leds show I/O on the RAM and ROM chips.
ROM and RAM chips Expose 2x64kb of memory via bank switching Addresses are set via two 74HC273 buffers Bank switching via two D-type flip-flops

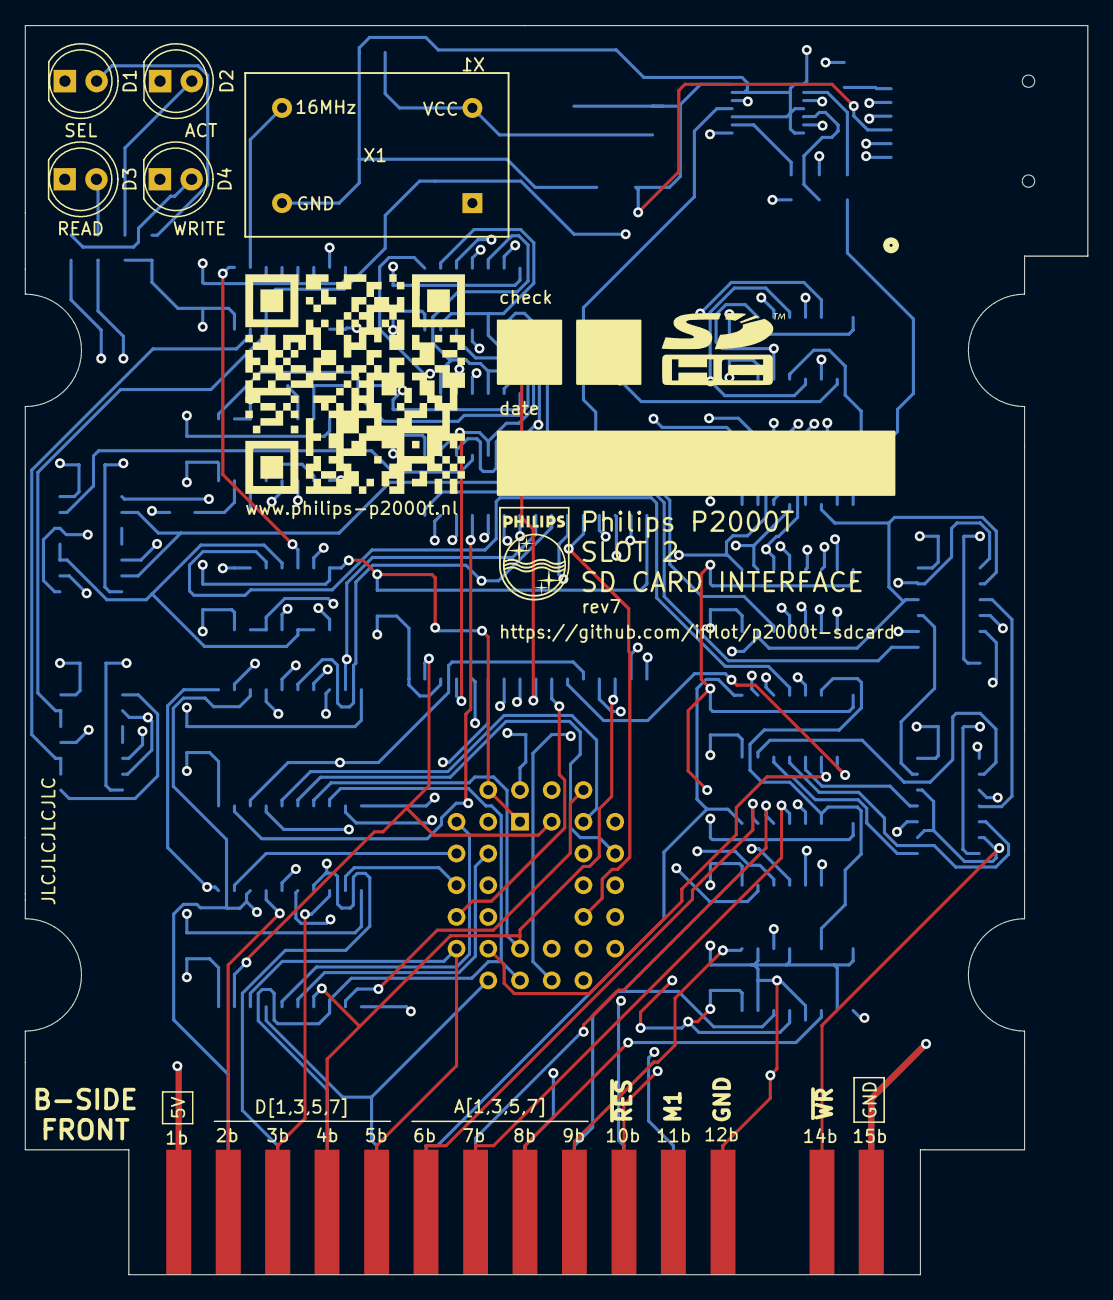
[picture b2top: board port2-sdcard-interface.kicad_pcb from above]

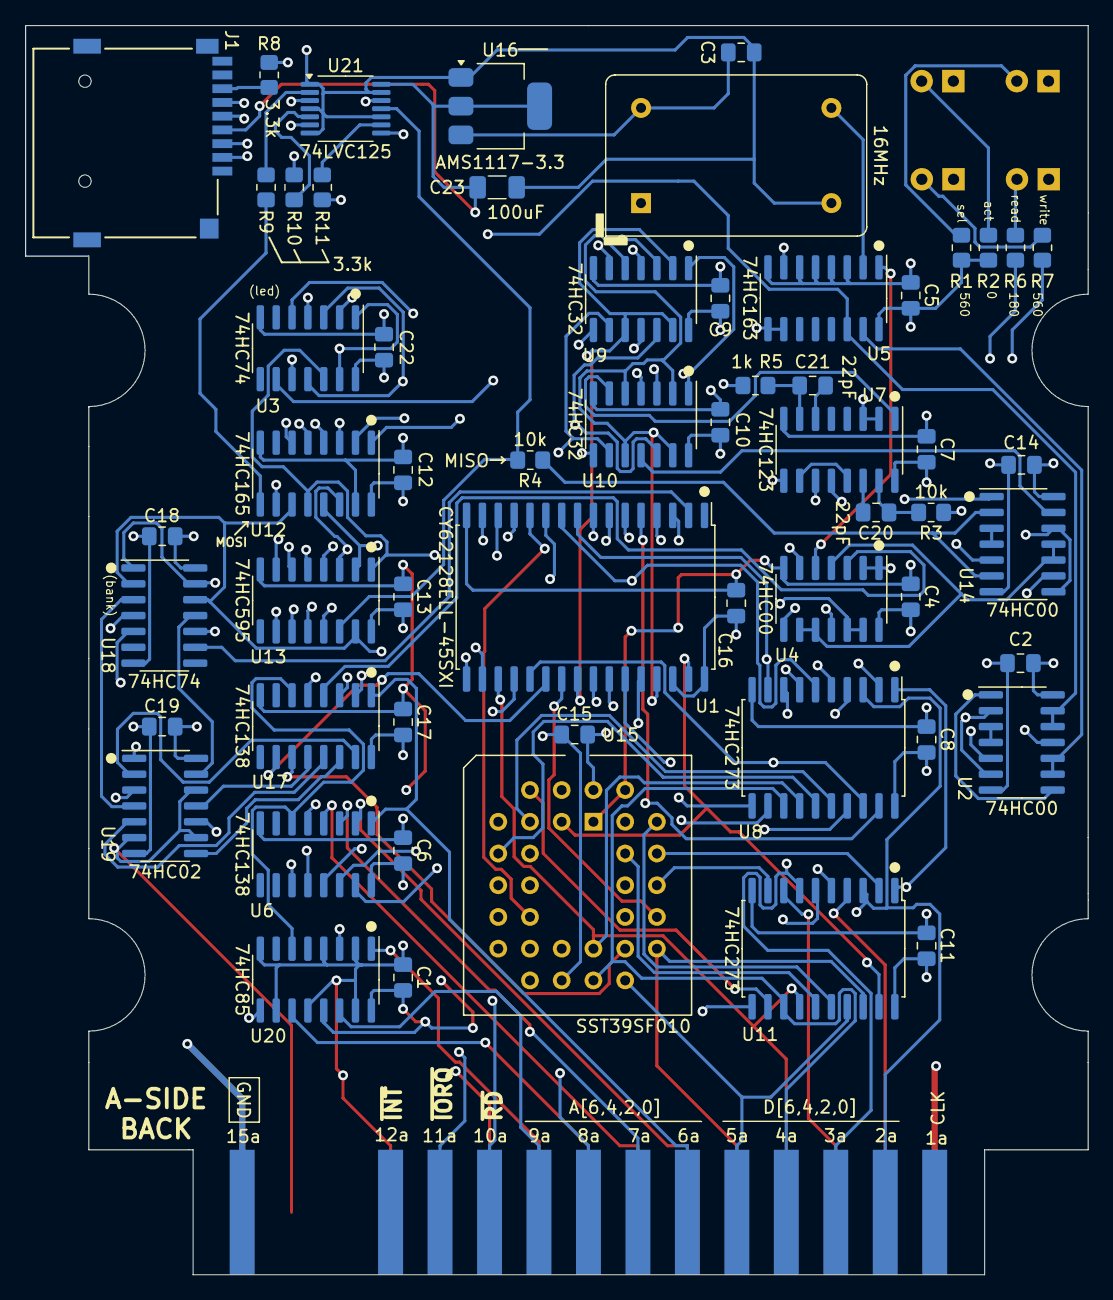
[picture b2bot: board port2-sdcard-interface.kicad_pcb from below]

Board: 4 copper layers, 85.1 x 100.0 mm, 65 parts (58 on the bottom side), 102 nets.

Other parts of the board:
G002: LOGO; qrcode
G003: LOGO; philips_logo
G004: LOGO; sdcard_logo

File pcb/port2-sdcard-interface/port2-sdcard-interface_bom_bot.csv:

Designator,Comment,Footprint,LCSC Part #
U21,74LVC125,Package_SO:TSSOP-14_4.4x5mm_P0.65mm,C6059
U16,AMS1117-3.3,Package_TO_SOT_SMD:SOT-223-3_TabPin2,C5346136
"R3,R4",10k,Resistor_SMD:R_0805_2012Metric_Pad1.20x1.40mm_HandSolder,C5159708
R5,1k,Resistor_SMD:R_0805_2012Metric_Pad1.20x1.40mm_HandSolder,C5123594
U1, CY62128ELL-45SXI,Package_SO:SSOP-32_11.305x20.495mm_P1.27mm,C2840304
"U2,U4,U14",74HC00,Package_SO:SO-14_3.9x8.65mm_P1.27mm,C699445
"C20,C21",22pF,Capacitor_SMD:C_0805_2012Metric_Pad1.18x1.45mm_HandSolder,C525286
R2,0,Resistor_SMD:R_0805_2012Metric_Pad1.20x1.40mm_HandSolder,C431818
R6,180,Resistor_SMD:R_0805_2012Metric_Pad1.20x1.40mm_HandSolder,C25270
"R1,R7",560,Resistor_SMD:R_0805_2012Metric_Pad1.20x1.40mm_HandSolder,C429158
"R8,R9,R10,R11",3.3k,Resistor_SMD:R_0805_2012Metric_Pad1.20x1.40mm_HandSolder,C407459
J1,Micro_SD_Card_Det1,components:CONN9_MSD-1_CUD,C381082
U5,74HC163,Package_SO:SOIC-16_3.9x9.9mm_P1.27mm,C338758
C23,100nF,Capacitor_SMD:C_1206_3216Metric_Pad1.33x1.80mm_HandSolder,C309030
"U8,U11",74HC273,Package_SO:SOIC-20W_7.5x12.8mm_P1.27mm,C131486
"C1,C2,C3,C4,C5,C6,C7,C8,C9,C10,C11,C12,C13,C14,C15,C16,C17,C18,C19,C22",0.1uF,Capacitor_SMD:C_0805_2012Metric_Pad1.18x1.45mm_HandSolder,C126469
"U3,U18",74HC74,Package_SO:SO-14_3.9x8.65mm_P1.27mm,C27597
U20,74HC85,Package_SO:SOIC-16_3.9x9.9mm_P1.27mm,C5953
U13,74HC595,Package_SO:SOIC-16_3.9x9.9mm_P1.27mm,C5947
"U9,U10",74HC32,Package_SO:SO-14_3.9x8.65mm_P1.27mm,C5632
U12,74HC165,Package_SO:SOIC-16_3.9x9.9mm_P1.27mm,C5613
"U6,U17",74HC138,Package_SO:SOIC-16_3.9x9.9mm_P1.27mm,C5602
U7,74HC123,Package_SO:SOIC-16_3.9x9.9mm_P1.27mm,C5597
U19,74HC02,Package_SO:SO-14_3.9x8.65mm_P1.27mm,C5588

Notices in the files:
README.md:
License: GPL v3
License: CC-BY-SA v4
